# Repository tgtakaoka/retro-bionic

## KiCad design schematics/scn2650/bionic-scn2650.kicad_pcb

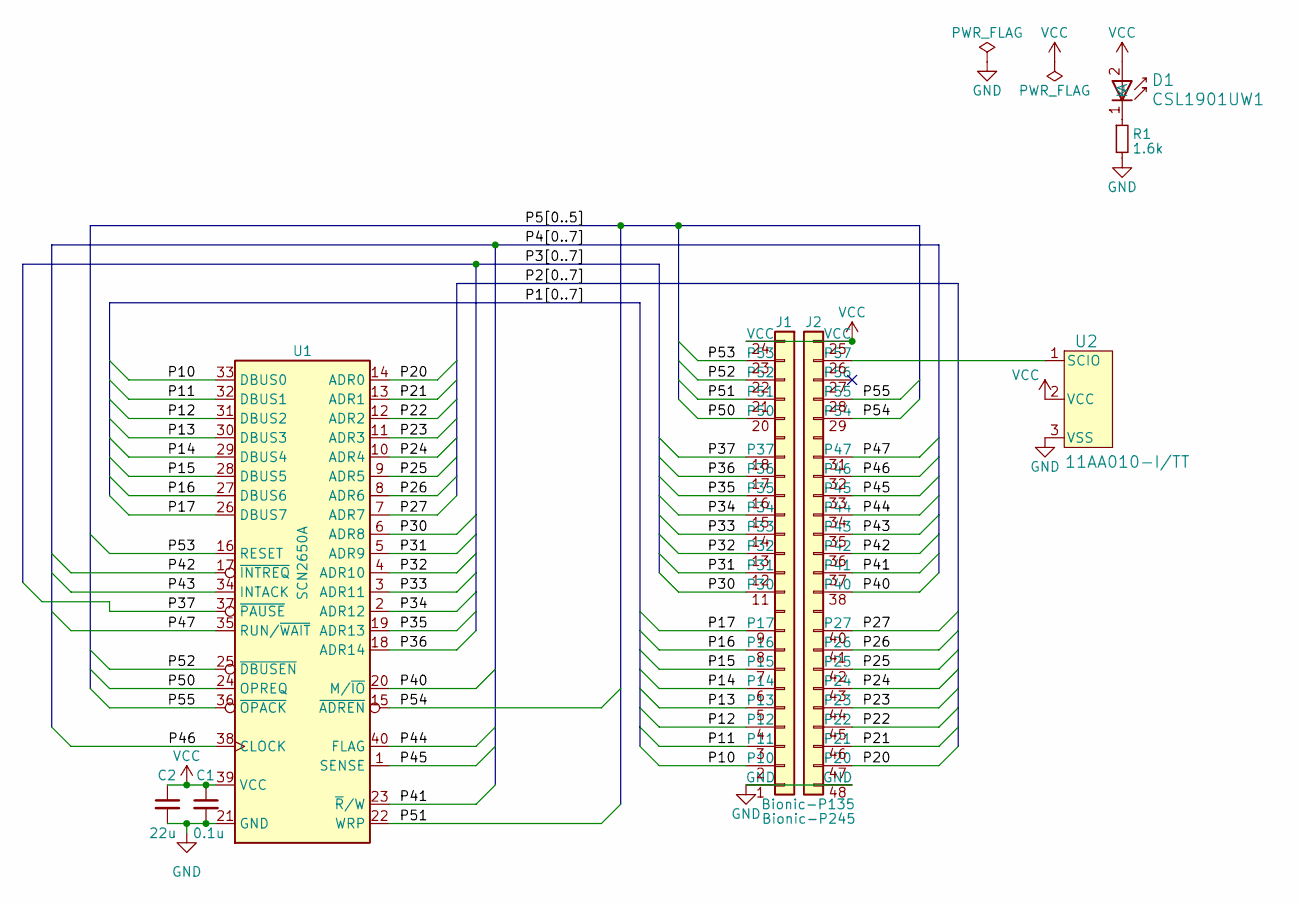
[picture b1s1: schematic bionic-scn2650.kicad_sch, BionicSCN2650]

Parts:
C1: 0.1u; C_0603_1608Metric_Pad1.08x0.95mm_HandSolder
C2: 22u; C_0603_1608Metric_Pad1.08x0.95mm_HandSolder
D1: CSL1901UW1; LED_CSL1901UW1_ROM-M
J1: Bionic-P135; Bionic-P135_THT
J2: Bionic-P245; Bionic-P245_THT
R1: 1.6k; R_0603_1608Metric_Pad0.98x0.95mm_HandSolder
U1: SCN2650A; DIP-40_W15.24mm_Socket
U2: 11AA010-I/TT; SOT-23_MC_MCH-M

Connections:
/P10: J1.2 (P10), U1.33 (DBUS0)
/P11: J1.3 (P11), U1.32 (DBUS1)
/P12: J1.4 (P12), U1.31 (DBUS2)
/P13: J1.5 (P13), U1.30 (DBUS3)
/P14: J1.6 (P14), U1.29 (DBUS4)
/P15: J1.7 (P15), U1.28 (DBUS5)
/P16: J1.8 (P16), U1.27 (DBUS6)
/P17: J1.9 (P17), U1.26 (DBUS7)
/P20: J2.47 (P20), U1.14 (ADR0)
/P21: J2.46 (P21), U1.13 (ADR1)
/P22: J2.45 (P22), U1.12 (ADR2)
/P23: J2.44 (P23), U1.11 (ADR3)
/P24: J2.43 (P24), U1.10 (ADR4)
/P25: J2.42 (P25), U1.9 (ADR5)
/P26: J2.41 (P26), U1.8 (ADR6)
/P27: J2.40 (P27), U1.7 (ADR7)
/P30: J1.11 (P30), U1.6 (ADR8)
/P31: J1.12 (P31), U1.5 (ADR9)
/P32: J1.13 (P32), U1.4 (ADR10)
/P33: J1.14 (P33), U1.3 (ADR11)
/P34: J1.15 (P34), U1.2 (ADR12)
/P35: J1.16 (P35), U1.19 (ADR13)
/P36: J1.17 (P36), U1.18 (ADR14)
/P37: J1.18 (P37), U1.37 (~PAUSE)
/P40: J2.38 (P40), U1.20 (M/~IO)
/P41: J2.37 (P41), U1.23 (~R/W)
/P42: J2.36 (P42), U1.17 (~INTREQ)
/P43: J2.35 (P43), U1.34 (INTACK)
/P44: J2.34 (P44), U1.40 (FLAG)
/P45: J2.33 (P45), U1.1 (SENSE)
/P46: J2.32 (P46), U1.38 (CLOCK)
/P47: J2.31 (P47), U1.35 (RUN/~WAIT)
/P50: J1.20 (P50), U1.24 (OPREQ)
/P51: J1.21 (P51), U1.22 (WRP)
/P52: J1.22 (P52), U1.25 (~DBUSEN)
/P53: J1.23 (P53), U1.16 (RESET)
/P54: J2.29 (P54), U1.15 (~ADREN)
/P55: J2.28 (P55), U1.36 (~OPACK)
GND: C1.2, C2.2, J1.1 (GND), J2.48 (GND), R1.2, U1.21 (GND), U2.3 (VSS)
unnamed: D1.1 (K), R1.1
unnamed: J2.26 (P57), U2.1 (SCIO)
VCC: C1.1, C2.1, D1.2 (A), J1.24 (VCC), J2.25 (VCC), U1.39 (VCC), U2.2 (VCC)

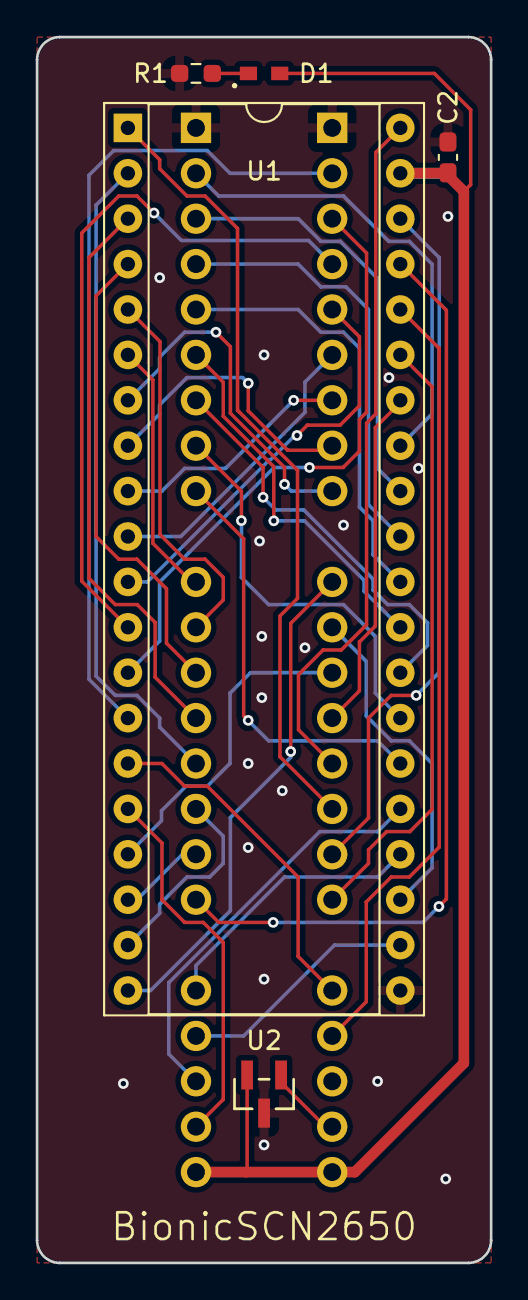
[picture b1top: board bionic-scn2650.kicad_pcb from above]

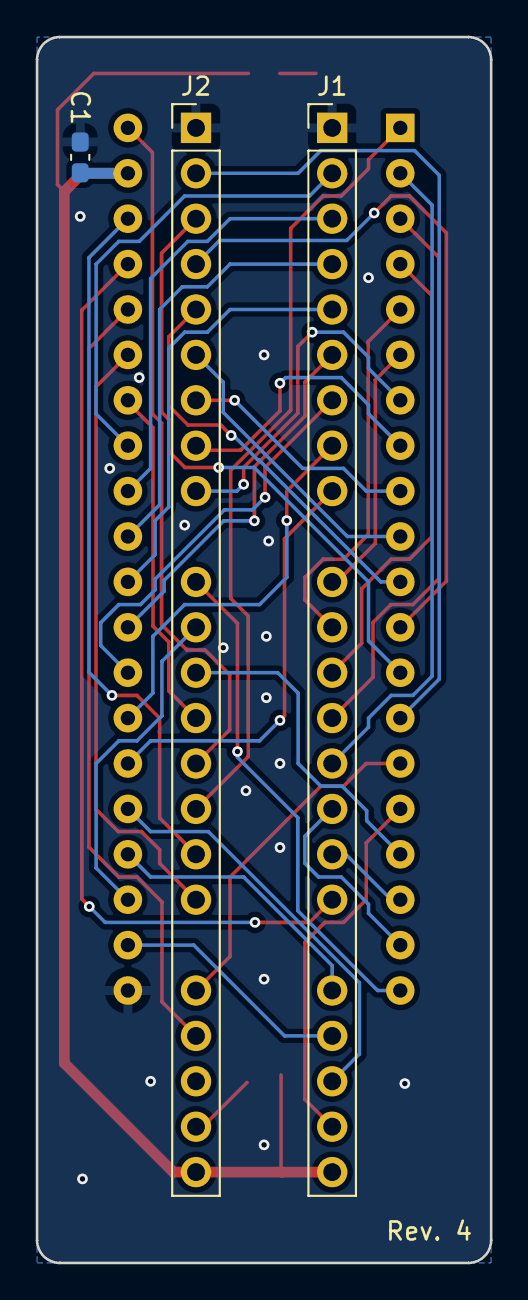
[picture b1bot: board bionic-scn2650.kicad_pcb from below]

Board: 2 copper layers, 25.4 x 68.6 mm, 8 parts (3 on the bottom side), 42 nets.

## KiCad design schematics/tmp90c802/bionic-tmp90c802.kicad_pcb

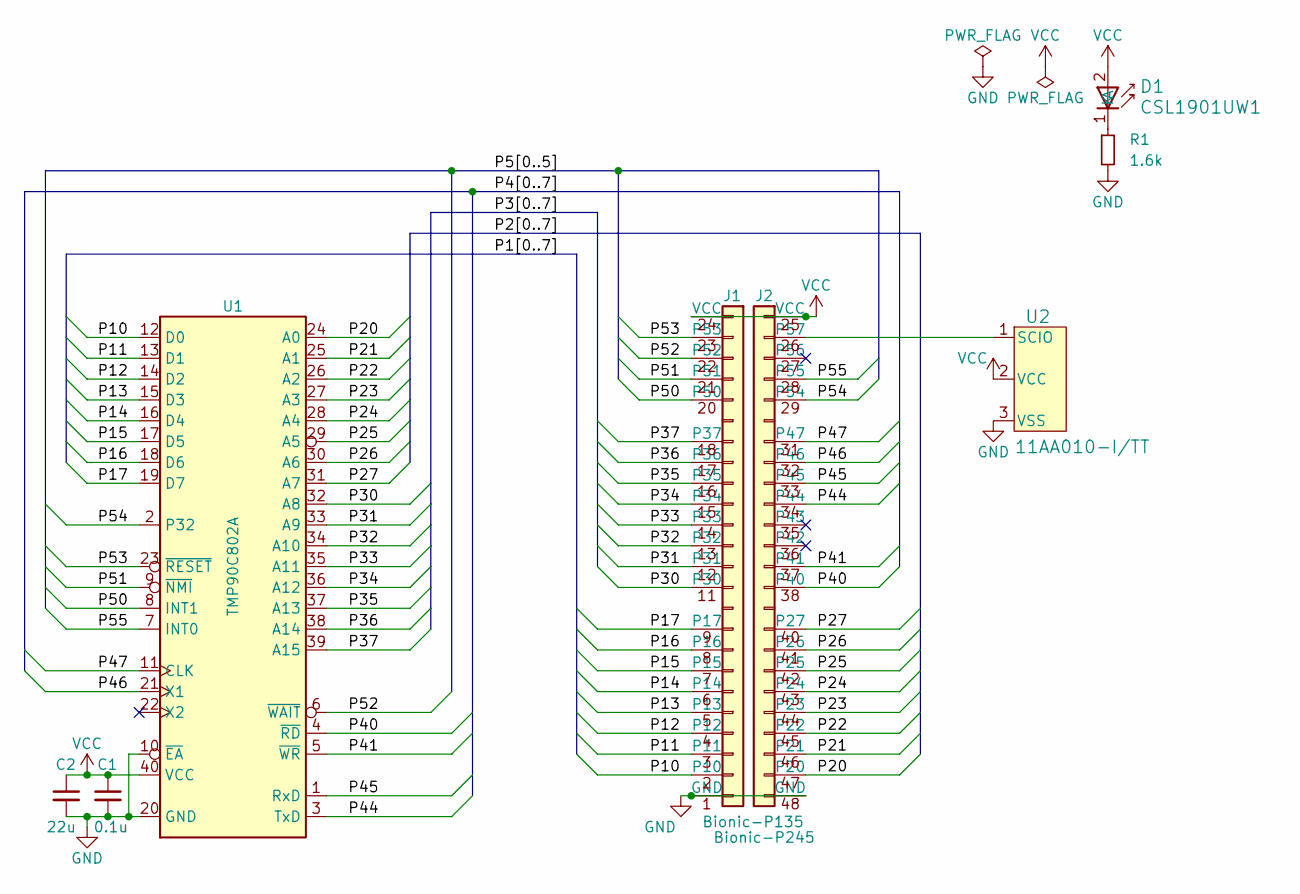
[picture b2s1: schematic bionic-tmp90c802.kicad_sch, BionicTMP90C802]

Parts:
C1: 0.1u; C_0603_1608Metric_Pad1.08x0.95mm_HandSolder
C2: 22u; C_0603_1608Metric_Pad1.08x0.95mm_HandSolder
D1: CSL1901UW1; LED_CSL1901UW1_ROM-M
J1: Bionic-P135; Bionic-P135_THT
J2: Bionic-P245; Bionic-P245_THT
R1: 1.6k; R_0603_1608Metric_Pad0.98x0.95mm_HandSolder
U1: TMP90C802A; DIP-40_W15.24mm_Socket
U2: 11AA010-I/TT; SOT-23_MC_MCH-M

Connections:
/P10: J1.2 (P10), U1.12 (D0)
/P11: J1.3 (P11), U1.13 (D1)
/P12: J1.4 (P12), U1.14 (D2)
/P13: J1.5 (P13), U1.15 (D3)
/P14: J1.6 (P14), U1.16 (D4)
/P15: J1.7 (P15), U1.17 (D5)
/P16: J1.8 (P16), U1.18 (D6)
/P17: J1.9 (P17), U1.19 (D7)
/P20: J2.47 (P20), U1.24 (A0)
/P21: J2.46 (P21), U1.25 (A1)
/P22: J2.45 (P22), U1.26 (A2)
/P23: J2.44 (P23), U1.27 (A3)
/P24: J2.43 (P24), U1.28 (A4)
/P25: J2.42 (P25), U1.29 (A5)
/P26: J2.41 (P26), U1.30 (A6)
/P27: J2.40 (P27), U1.31 (A7)
/P30: J1.11 (P30), U1.32 (A8)
/P31: J1.12 (P31), U1.33 (A9)
/P32: J1.13 (P32), U1.34 (A10)
/P33: J1.14 (P33), U1.35 (A11)
/P34: J1.15 (P34), U1.36 (A12)
/P35: J1.16 (P35), U1.37 (A13)
/P36: J1.17 (P36), U1.38 (A14)
/P37: J1.18 (P37), U1.39 (A15)
/P40: J2.38 (P40), U1.4 (~RD)
/P41: J2.37 (P41), U1.5 (~WR)
/P44: J2.34 (P44), U1.3 (TxD)
/P45: J2.33 (P45), U1.1 (RxD)
/P46: J2.32 (P46), U1.21 (X1)
/P47: J2.31 (P47), U1.11 (CLK)
/P50: J1.20 (P50), U1.8 (INT1)
/P51: J1.21 (P51), U1.9 (~NMI)
/P52: J1.22 (P52), U1.6 (~WAIT)
/P53: J1.23 (P53), U1.23 (~RESET)
/P54: J2.29 (P54), U1.2 (P32)
/P55: J2.28 (P55), U1.7 (INT0)
GND: C1.2, C2.2, J1.1 (GND), J2.48 (GND), R1.2, U1.10 (~EA), U1.20 (GND), U2.3 (VSS)
unnamed: D1.1 (K), R1.1
unnamed: J2.26 (P57), U2.1 (SCIO)
VCC: C1.1, C2.1, D1.2 (A), J1.24 (VCC), J2.25 (VCC), U1.40 (VCC), U2.2 (VCC)

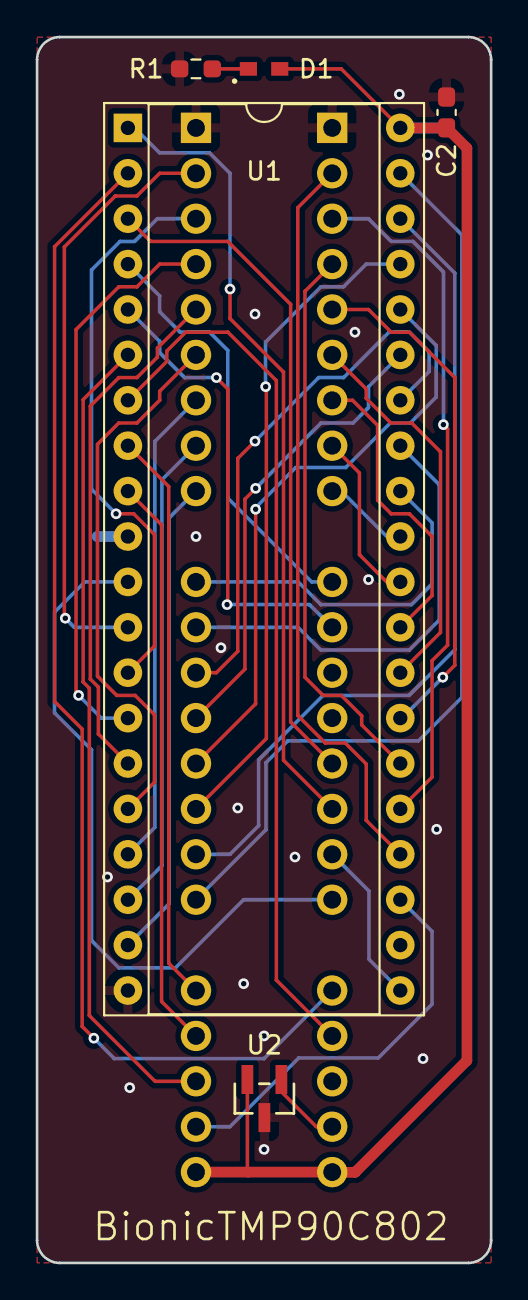
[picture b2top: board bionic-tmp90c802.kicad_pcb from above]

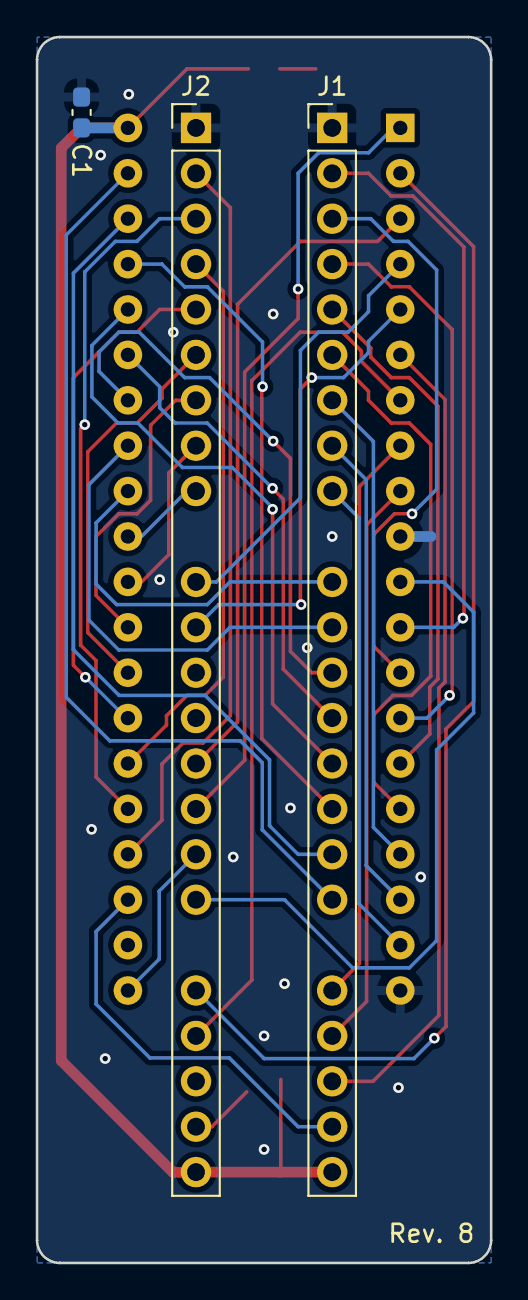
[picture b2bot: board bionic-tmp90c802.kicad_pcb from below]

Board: 2 copper layers, 25.4 x 68.6 mm, 8 parts (3 on the bottom side), 40 nets.

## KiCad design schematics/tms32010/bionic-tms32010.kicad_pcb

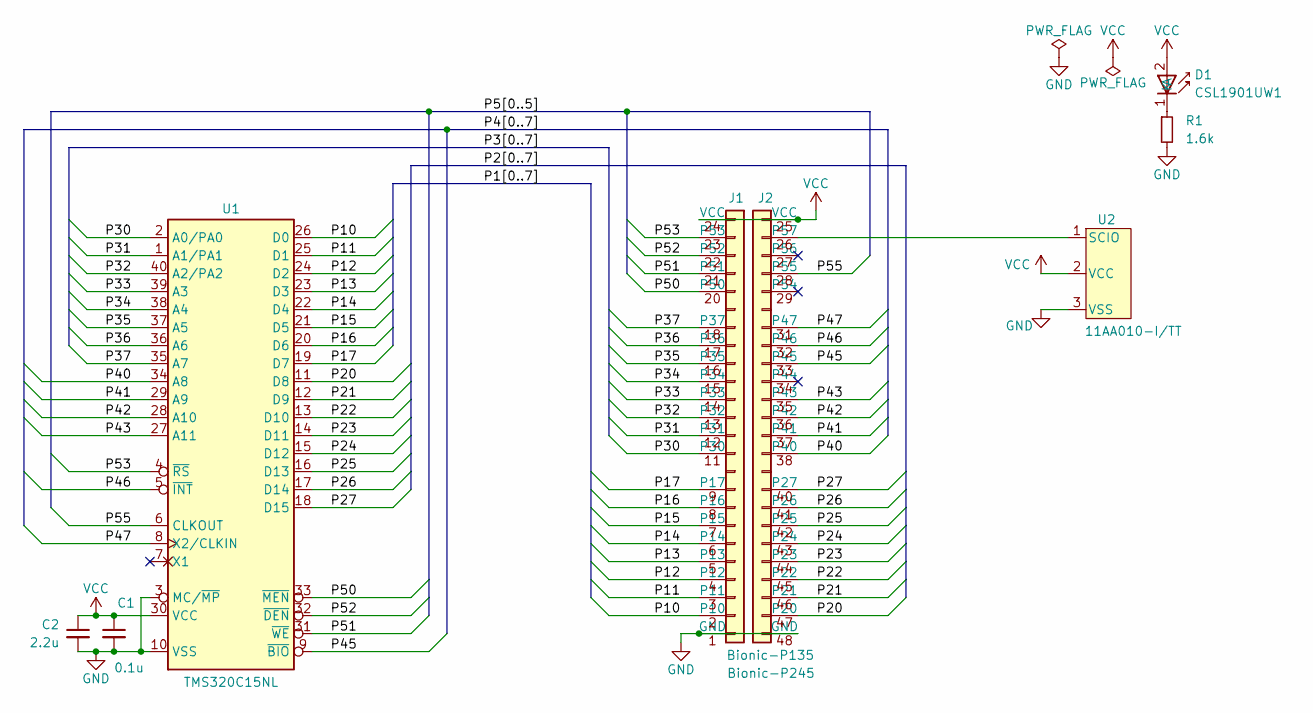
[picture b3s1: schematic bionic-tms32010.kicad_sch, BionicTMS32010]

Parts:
C1: 0.1u; C_0603_1608Metric_Pad1.08x0.95mm_HandSolder
C2: 2.2u; C_0603_1608Metric_Pad1.08x0.95mm_HandSolder
D1: CSL1901UW1; LED_CSL1901UW1_ROM-M
J1: Bionic-P135; Bionic-P135_THT
J2: Bionic-P245; Bionic-P245_THT
R1: 1.6k; R_0603_1608Metric_Pad0.98x0.95mm_HandSolder
U1: TMS320C15NL; DIP-40_W15.24mm_Socket
U2: 11AA010-I/TT; SOT-23_MC_MCH-M

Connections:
/P10: J1.2 (P10), U1.26 (D0)
/P11: J1.3 (P11), U1.25 (D1)
/P12: J1.4 (P12), U1.24 (D2)
/P13: J1.5 (P13), U1.23 (D3)
/P14: J1.6 (P14), U1.22 (D4)
/P15: J1.7 (P15), U1.21 (D5)
/P16: J1.8 (P16), U1.20 (D6)
/P17: J1.9 (P17), U1.19 (D7)
/P20: J2.47 (P20), U1.11 (D8)
/P21: J2.46 (P21), U1.12 (D9)
/P22: J2.45 (P22), U1.13 (D10)
/P23: J2.44 (P23), U1.14 (D11)
/P24: J2.43 (P24), U1.15 (D12)
/P25: J2.42 (P25), U1.16 (D13)
/P26: J2.41 (P26), U1.17 (D14)
/P27: J2.40 (P27), U1.18 (D15)
/P30: J1.11 (P30), U1.2 (A0/PA0)
/P31: J1.12 (P31), U1.1 (A1/PA1)
/P32: J1.13 (P32), U1.40 (A2/PA2)
/P33: J1.14 (P33), U1.39 (A3)
/P34: J1.15 (P34), U1.38 (A4)
/P35: J1.16 (P35), U1.37 (A5)
/P36: J1.17 (P36), U1.36 (A6)
/P37: J1.18 (P37), U1.35 (A7)
/P40: J2.38 (P40), U1.34 (A8)
/P41: J2.37 (P41), U1.29 (A9)
/P42: J2.36 (P42), U1.28 (A10)
/P43: J2.35 (P43), U1.27 (A11)
/P45: J2.33 (P45), U1.9 (~BIO)
/P46: J2.32 (P46), U1.5 (~INT)
/P47: J2.31 (P47), U1.8 (X2/CLKIN)
/P50: J1.20 (P50), U1.33 (~MEN)
/P51: J1.21 (P51), U1.31 (~WE)
/P52: J1.22 (P52), U1.32 (~DEN)
/P53: J1.23 (P53), U1.4 (~RS)
/P55: J2.28 (P55), U1.6 (CLKOUT)
GND: C1.2, C2.2, J1.1 (GND), J2.48 (GND), R1.2, U1.3 (MC/~MP), U1.10 (VSS), U2.3 (VSS)
unnamed: D1.1 (K), R1.1
unnamed: J2.26 (P57), U2.1 (SCIO)
VCC: C1.1, C2.1, D1.2 (A), J1.24 (VCC), J2.25 (VCC), U1.30 (VCC), U2.2 (VCC)

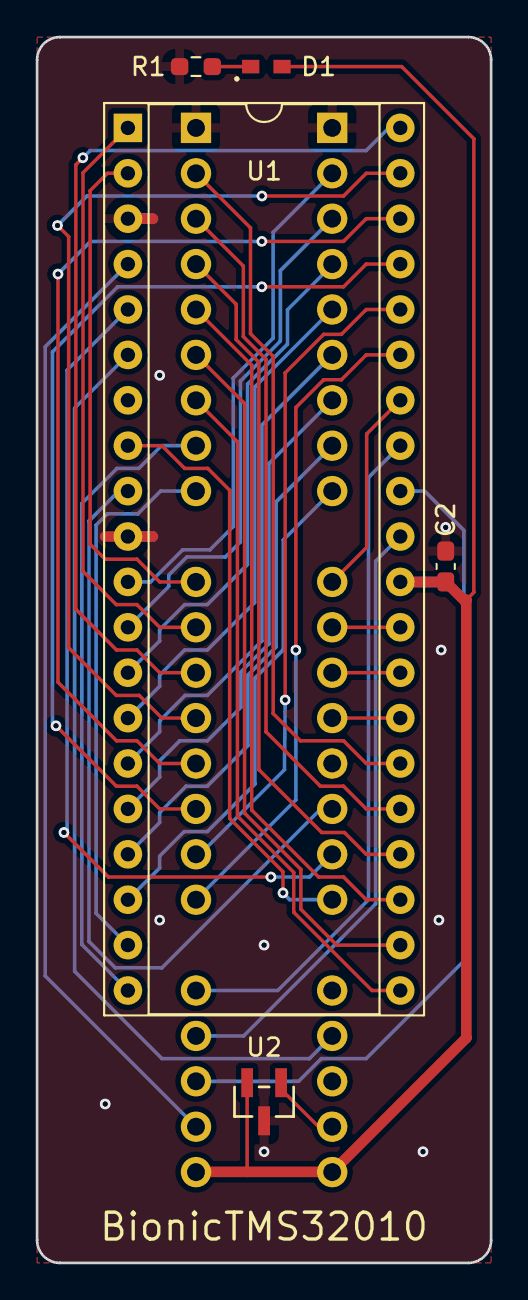
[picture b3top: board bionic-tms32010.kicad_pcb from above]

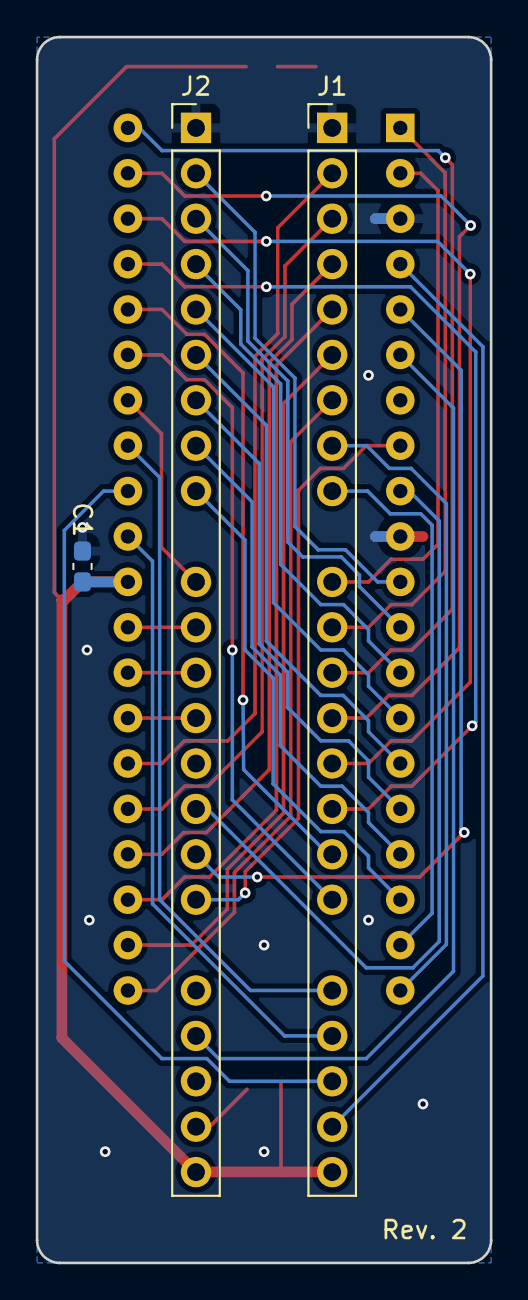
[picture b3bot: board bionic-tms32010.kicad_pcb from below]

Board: 2 copper layers, 25.4 x 68.6 mm, 8 parts (3 on the bottom side), 40 nets.

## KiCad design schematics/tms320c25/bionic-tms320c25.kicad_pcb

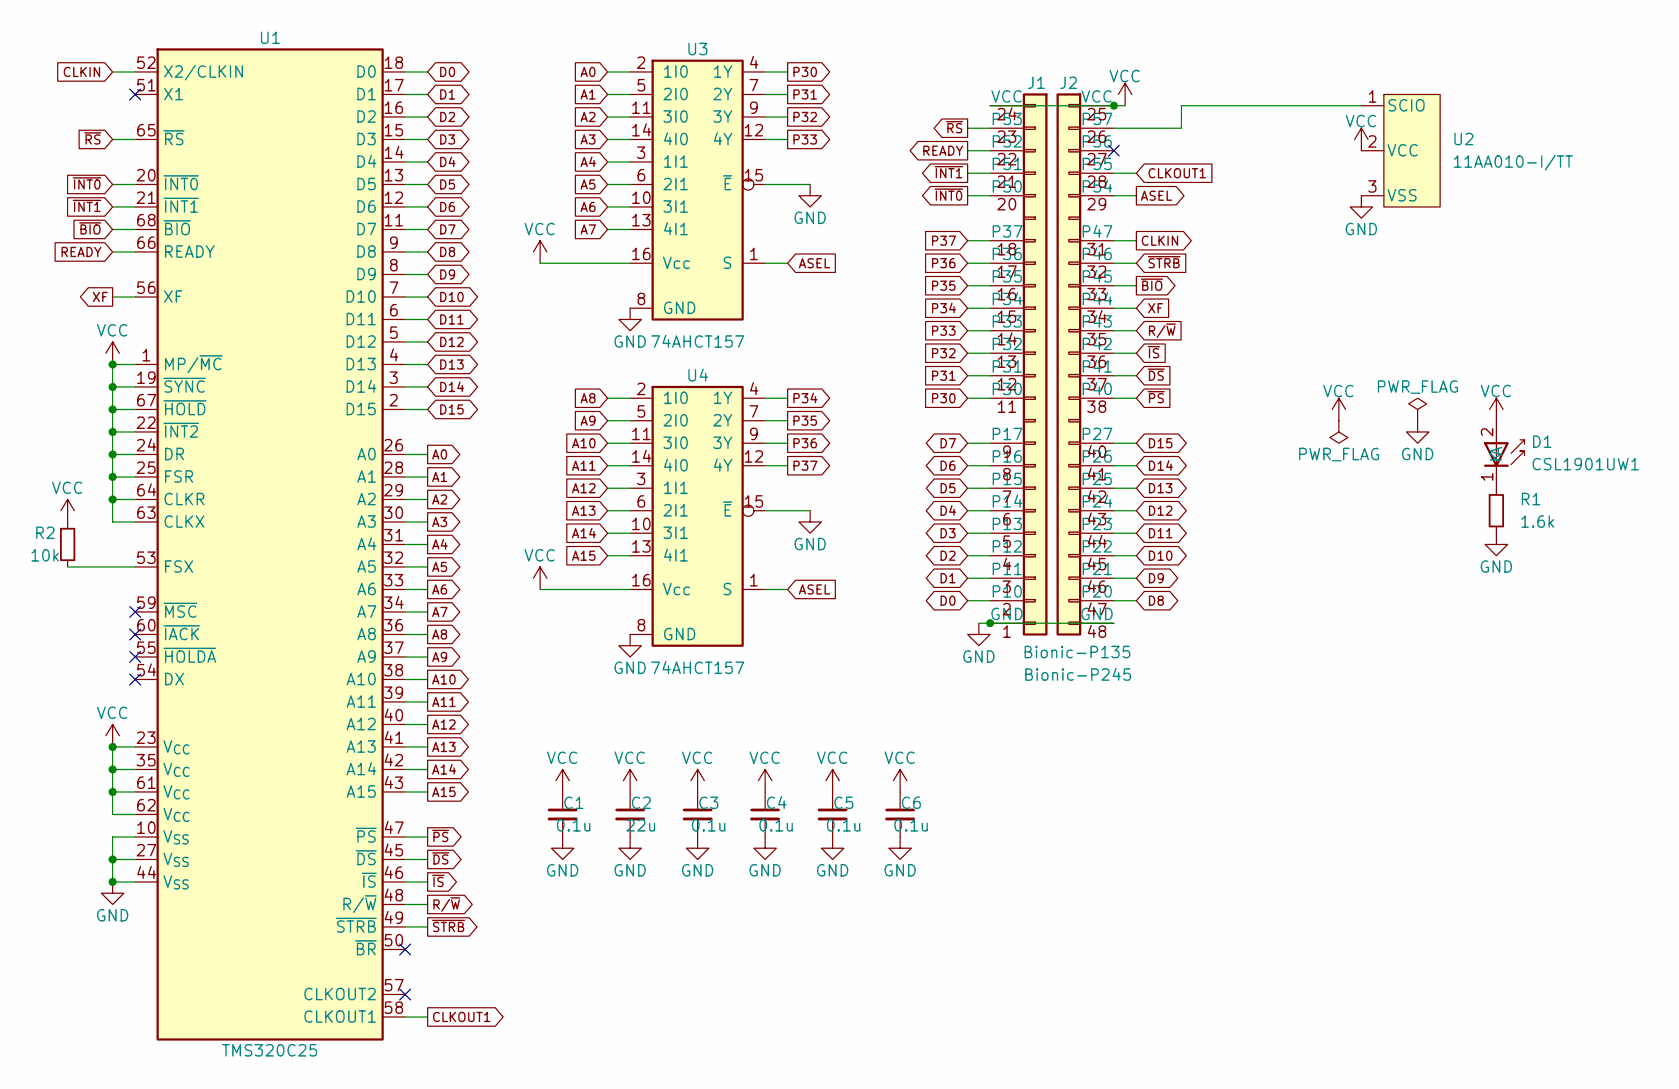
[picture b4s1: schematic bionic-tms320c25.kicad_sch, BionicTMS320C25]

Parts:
C1, C3, C4, C5, C6: 0.1u; C_0603_1608Metric_Pad1.08x0.95mm_HandSolder
C2: 22u; C_0603_1608Metric_Pad1.08x0.95mm_HandSolder
D1: CSL1901UW1; LED_CSL1901UW1_ROM-M
J1: Bionic-P135; Bionic-P135_SMT
J2: Bionic-P245; Bionic-P245_SMT
R1: 1.6k; R_0603_1608Metric_Pad0.98x0.95mm_HandSolder
R2: 10k; R_0603_1608Metric_Pad0.98x0.95mm_HandSolder
U1: TMS320C25; 846821B1RKTP
U2: 11AA010-I/TT; SOT-23_MC_MCH-M
U3, U4: 74AHCT157; PW16-M

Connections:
A0: U1.26 (HSI.2/HSO.4), U3.2 (1I0)
A1: U1.28 (HSO.0), U3.5 (2I0)
A2: U1.29 (HSO.1), U3.11 (3I0)
A3: U1.30 (P1.5), U3.14 (4I0)
A4: U1.31 (P1.6), U3.3 (1I1)
A5: U1.32 (P1.7), U3.6 (2I1)
A6: U1.33 (P2.6), U3.10 (3I1)
A7: U1.34 (HSO.2), U3.13 (4I1)
A8: U1.36 (V_{SS}), U4.2 (1I0)
A9: U1.37 (V_{PP}), U4.5 (2I0)
A10: U1.38 (P2.7), U4.11 (3I0)
A11: U1.39 (P2.5/PWM), U4.14 (4I0)
A12: U1.40 (~WRL/~WR), U4.3 (1I1)
A13: U1.41 (~WRH/~BHE), U4.6 (2I1)
A14: U1.42 (P2.4/T2RST), U4.10 (3I1)
A15: U1.43 (READY), U4.13 (4I1)
ASEL: J2.29 (P54), U3.1 (S), U4.1 (S)
CLKIN: J2.31 (P47), U1.52 (AD8)
CLKOUT1: J2.28 (P55), U1.58 (AD2)
D0: J1.2 (P10), U1.18 (P2.0/TxD)
D1: J1.3 (P11), U1.17 (P2.1/RxD)
D2: J1.4 (P12), U1.16 (~RESET)
D3: J1.5 (P13), U1.15 (P2.2/EXINT)
D4: J1.6 (P14), U1.14 (V_{PD})
D5: J1.7 (P15), U1.13 (V_{REF})
D6: J1.8 (P16), U1.12 (ANGND)
D7: J1.9 (P17), U1.11 (ACH4)
D8: J2.47 (P20), U1.9 (ACH7)
D9: J2.46 (P21), U1.8 (ACH6)
D10: J2.45 (P22), U1.7 (ACH2)
D11: J2.44 (P23), U1.6 (ACH0)
D12: J2.43 (P24), U1.5 (ACH1)
D13: J2.42 (P25), U1.4 (ACH3)
D14: J2.41 (P26), U1.3 (NMI)
D15: J2.40 (P27), U1.2 (~EA)
GND: C1.2, C2.2, C3.2, C4.2, C5.2, C6.2, J1.1 (GND), J2.48 (GND), R1.2, U1.10 (ACH5), U1.27 (HSI.3/HSO.5), U1.44 (P2.3/T2CLK), U2.3 (VSS), U3.8 (GND), U3.15 (~E), U4.8 (GND), U4.15 (~E)
unnamed: D1.1 (K), R1.1
unnamed: J2.26 (P57), U2.1 (SCIO)
unnamed: R2.2, U1.53 (AD7)
P30: J1.11 (P30), U3.4 (1Y)
P31: J1.12 (P31), U3.7 (2Y)
P32: J1.13 (P32), U3.9 (3Y)
P33: J1.14 (P33), U3.12 (4Y)
P34: J1.15 (P34), U4.4 (1Y)
P35: J1.16 (P35), U4.7 (2Y)
P36: J1.17 (P36), U4.9 (3Y)
P37: J1.18 (P37), U4.12 (4Y)
READY: J1.22 (P52), U1.66 (XTAL2)
R/~W: J2.35 (P43), U1.48 (AD12)
VCC: C1.1, C2.1, C3.1, C4.1, C5.1, C6.1, D1.2 (A), J1.24 (VCC), J2.25 (VCC), R2.1, U1.1 (V_{CC}), U1.19 (P1.0), U1.22 (P1.3), U1.23 (P1.4), U1.24 (HSI.0), U1.25 (HSI.1), U1.35 (HSO.3), U1.61 (~RD), U1.62 (~ALE/~ADV), U1.63 (INST), U1.64 (BUSWIDTH), U1.67 (XTAL1), U2.2 (VCC), U3.16 (Vcc), U4.16 (Vcc)
XF: J2.34 (P44), U1.56 (AD4)
~BIO: J2.33 (P45), U1.68 (V_{SS})
~DS: J2.37 (P41), U1.45 (AD15)
~INT0: J1.20 (P50), U1.20 (P1.1)
~INT1: J1.21 (P51), U1.21 (P1.2)
~IS: J2.36 (P42), U1.46 (AD14)
~PS: J2.38 (P40), U1.47 (AD13)
~RS: J1.23 (P53), U1.65 (CLKOUT)
~STRB: J2.32 (P46), U1.49 (AD11)

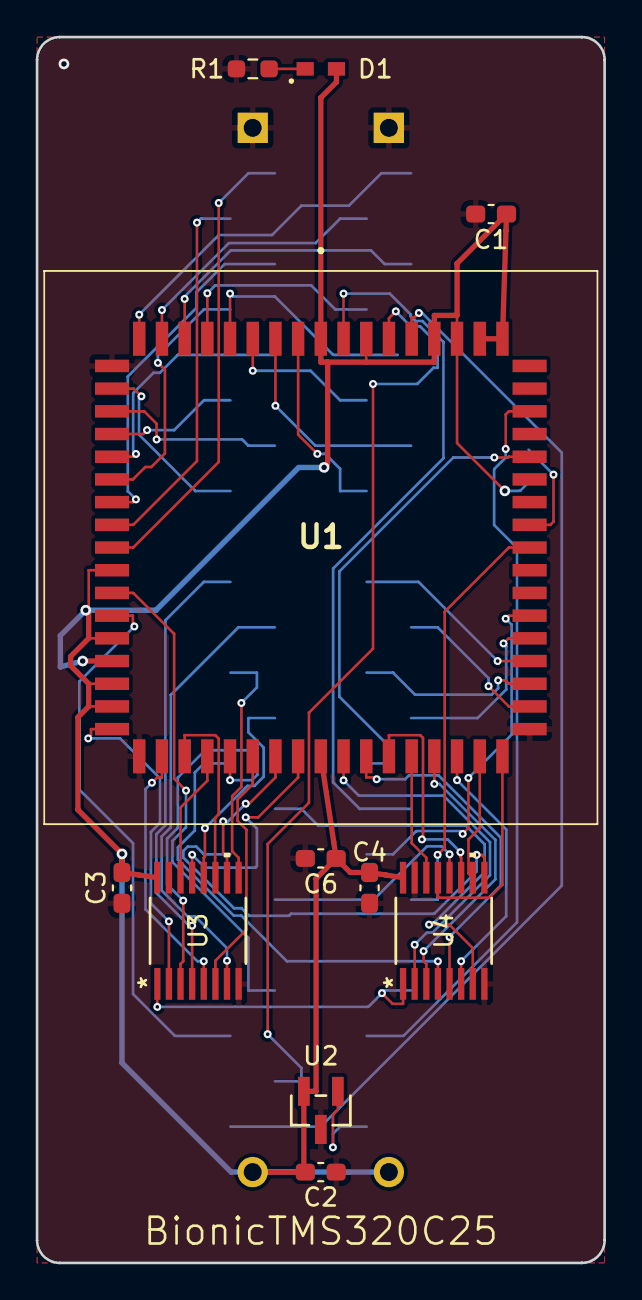
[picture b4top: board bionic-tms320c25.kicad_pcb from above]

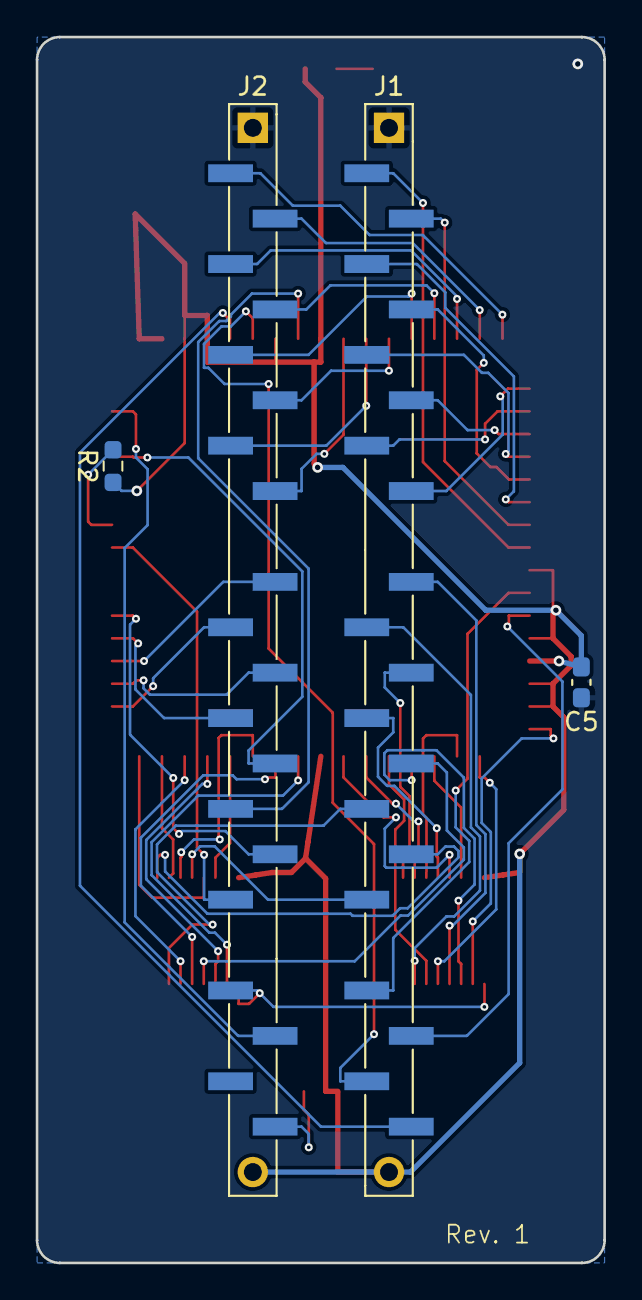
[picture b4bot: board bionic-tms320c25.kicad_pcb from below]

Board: 2 copper layers, 31.8 x 68.6 mm, 15 parts (4 on the bottom side), 59 nets.

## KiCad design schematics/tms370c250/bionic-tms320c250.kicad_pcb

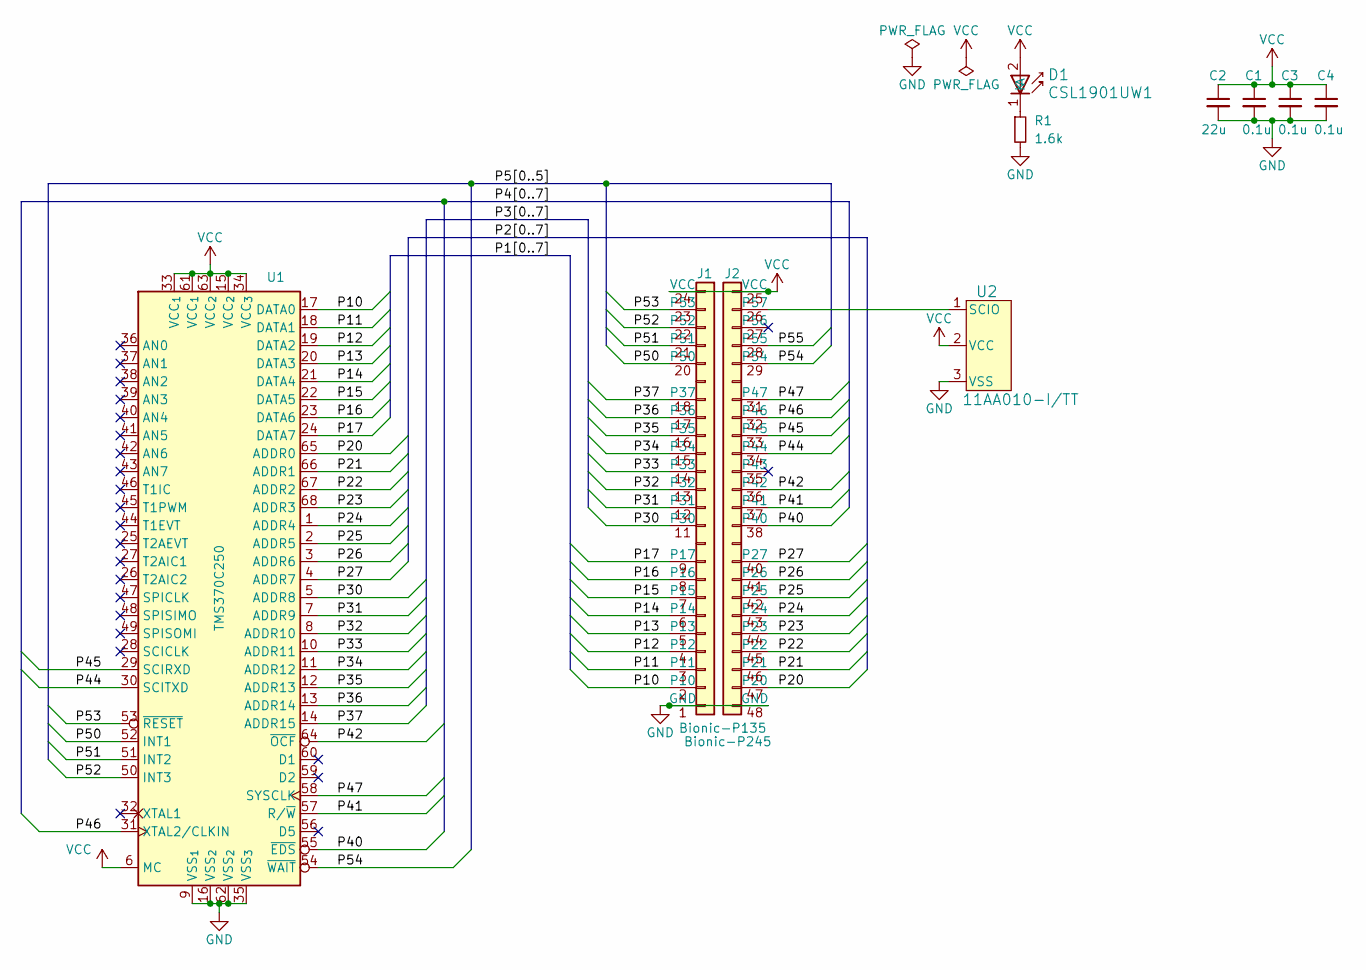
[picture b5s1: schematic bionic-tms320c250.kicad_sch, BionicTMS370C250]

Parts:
C1, C3, C4: 0.1u; C_0603_1608Metric_Pad1.08x0.95mm_HandSolder
C2: 22u; C_0603_1608Metric_Pad1.08x0.95mm_HandSolder
D1: CSL1901UW1; LED_CSL1901UW1_ROM-M
J1: Bionic-P135; Bionic-P135_SMT
J2: Bionic-P245; Bionic-P245_SMT
R1: 1.6k; R_0603_1608Metric_Pad0.98x0.95mm_HandSolder
U1: TMS370C250; 846821B1RKTP
U2: 11AA010-I/TT; SOT-23_MC_MCH-M

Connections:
/P10: J1.2 (P10), U1.17 (DATA0)
/P11: J1.3 (P11), U1.18 (DATA1)
/P12: J1.4 (P12), U1.19 (DATA2)
/P13: J1.5 (P13), U1.20 (DATA3)
/P14: J1.6 (P14), U1.21 (DATA4)
/P15: J1.7 (P15), U1.22 (DATA5)
/P16: J1.8 (P16), U1.23 (DATA6)
/P17: J1.9 (P17), U1.24 (DATA7)
/P20: J2.47 (P20), U1.65 (ADDR0)
/P21: J2.46 (P21), U1.66 (ADDR1)
/P22: J2.45 (P22), U1.67 (ADDR2)
/P23: J2.44 (P23), U1.68 (ADDR3)
/P24: J2.43 (P24), U1.1 (ADDR4)
/P25: J2.42 (P25), U1.2 (ADDR5)
/P26: J2.41 (P26), U1.3 (ADDR6)
/P27: J2.40 (P27), U1.4 (ADDR7)
/P30: J1.11 (P30), U1.5 (ADDR8)
/P31: J1.12 (P31), U1.7 (ADDR9)
/P32: J1.13 (P32), U1.8 (ADDR10)
/P33: J1.14 (P33), U1.10 (ADDR11)
/P34: J1.15 (P34), U1.11 (ADDR12)
/P35: J1.16 (P35), U1.12 (ADDR13)
/P36: J1.17 (P36), U1.13 (ADDR14)
/P37: J1.18 (P37), U1.14 (ADDR15)
/P40: J2.38 (P40), U1.55 (~EDS)
/P41: J2.37 (P41), U1.57 (R/~W)
/P42: J2.36 (P42), U1.64 (~OCF)
/P44: J2.34 (P44), U1.30 (SCITXD)
/P45: J2.33 (P45), U1.29 (SCIRXD)
/P46: J2.32 (P46), U1.31 (XTAL2/CLKIN)
/P47: J2.31 (P47), U1.58 (SYSCLK)
/P50: J1.20 (P50), U1.52 (INT1)
/P51: J1.21 (P51), U1.51 (INT2)
/P52: J1.22 (P52), U1.50 (INT3)
/P53: J1.23 (P53), U1.53 (~RESET)
/P54: J2.29 (P54), U1.54 (~WAIT)
/P55: J2.28 (P55)
GND: C1.2, C2.2, C3.2, C4.2, J1.1 (GND), J2.48 (GND), R1.2, U1.9 (VSS_{1}), U1.16 (VSS_{2}), U1.35 (VSS_{3}), U1.62 (VSS_{2}), U2.3 (VSS)
unnamed: D1.1 (K), R1.1
unnamed: J2.26 (P57), U2.1 (SCIO)
VCC: C1.1, C2.1, C3.1, C4.1, D1.2 (A), J1.24 (VCC), J2.25 (VCC), U1.6 (MC), U1.15 (VCC_{2}), U1.33 (VCC_{1}), U1.34 (VCC_{3}), U1.61 (VCC_{1}), U1.63 (VCC_{2}), U2.2 (VCC)

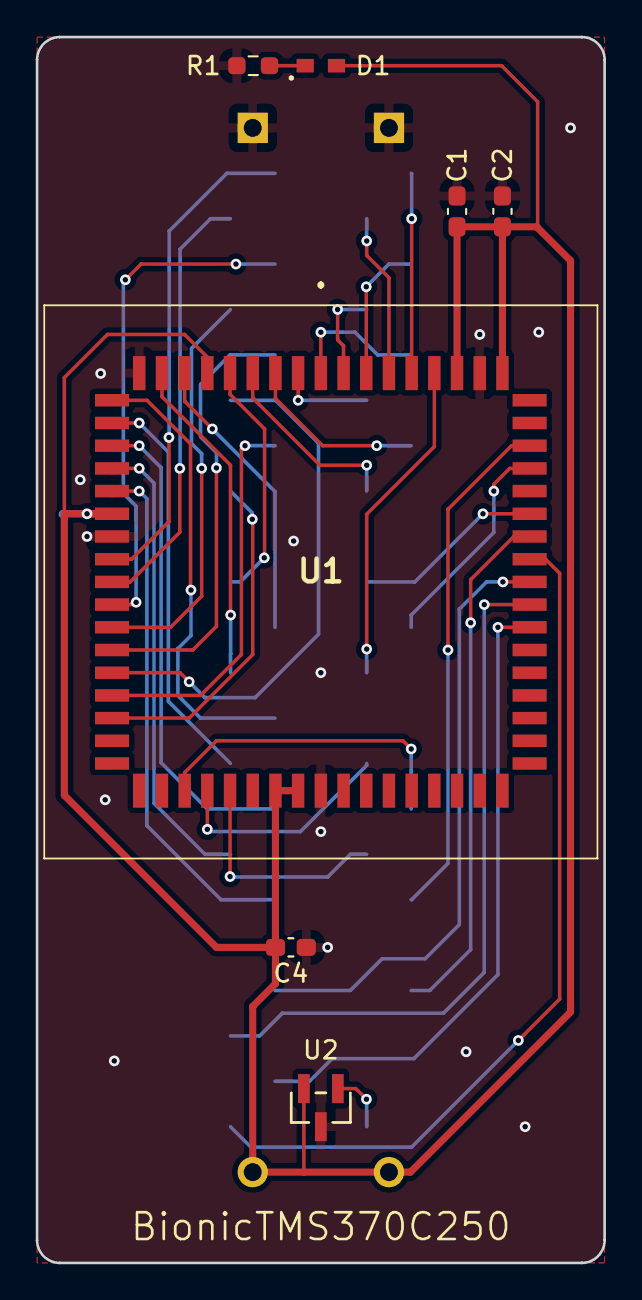
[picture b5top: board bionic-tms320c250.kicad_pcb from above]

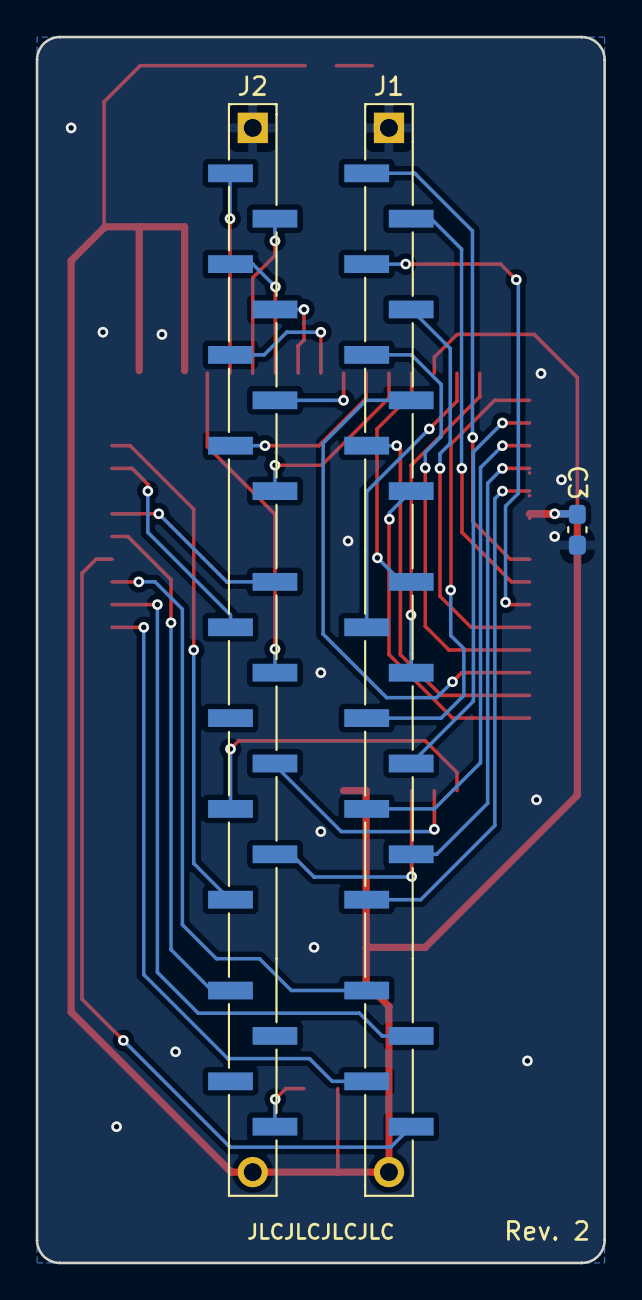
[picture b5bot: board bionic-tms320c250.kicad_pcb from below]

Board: 2 copper layers, 31.7 x 68.6 mm, 10 parts (3 on the bottom side), 40 nets.

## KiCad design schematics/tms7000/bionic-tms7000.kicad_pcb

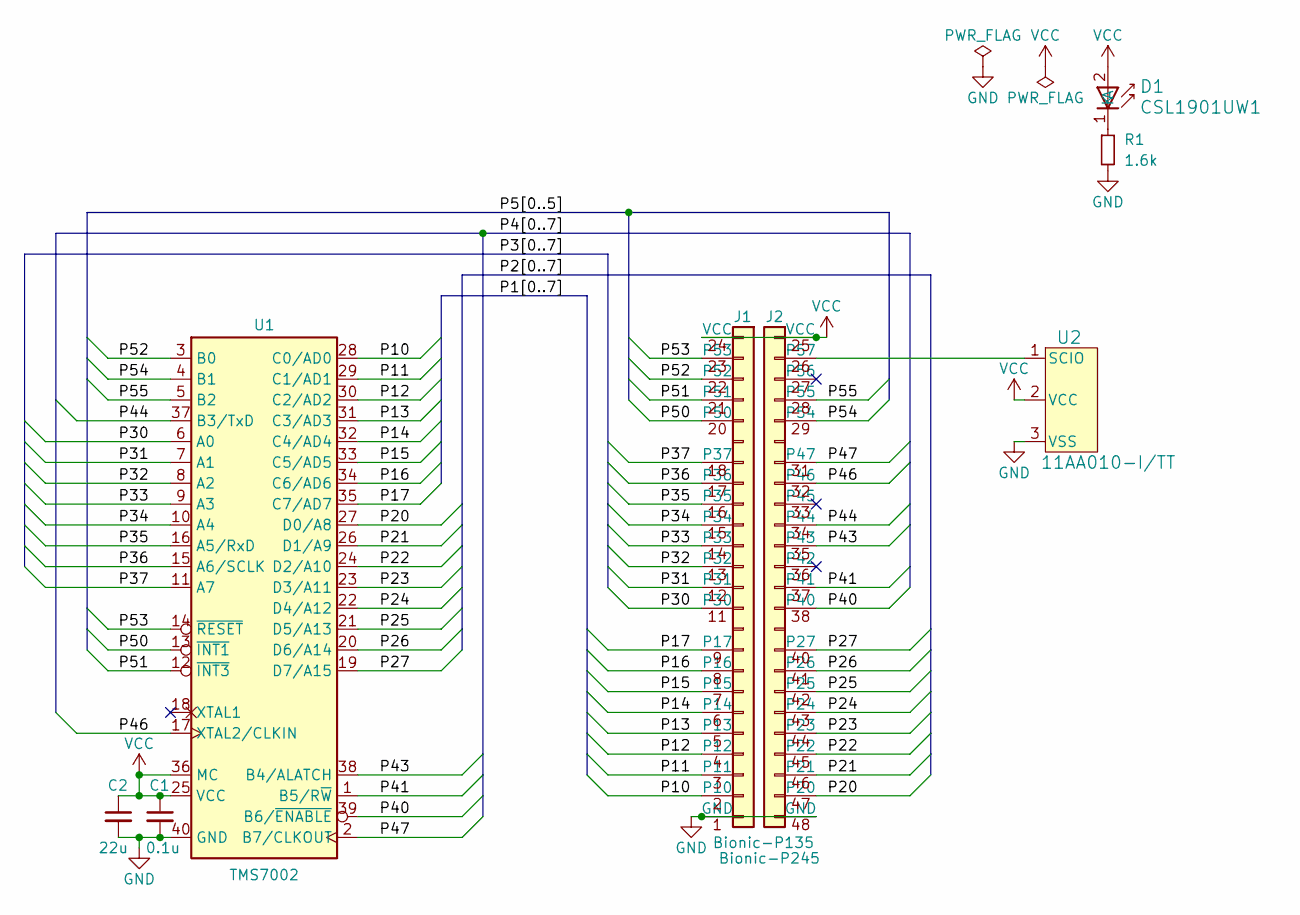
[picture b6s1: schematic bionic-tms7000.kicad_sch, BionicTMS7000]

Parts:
C1: 0.1u; C_0603_1608Metric_Pad1.08x0.95mm_HandSolder
C2: 22u; C_0603_1608Metric_Pad1.08x0.95mm_HandSolder
D1: CSL1901UW1; LED_CSL1901UW1_ROM-M
J1: Bionic-P135; Bionic-P135_THT
J2: Bionic-P245; Bionic-P245_THT
R1: 1.6k; R_0603_1608Metric_Pad0.98x0.95mm_HandSolder
U1: TMS7002; DIP-40_W15.24mm_Socket
U2: 11AA010-I/TT; SOT-23_MC_MCH-M

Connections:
/P10: J1.2 (P10), U1.28 (C0/AD0)
/P11: J1.3 (P11), U1.29 (C1/AD1)
/P12: J1.4 (P12), U1.30 (C2/AD2)
/P13: J1.5 (P13), U1.31 (C3/AD3)
/P14: J1.6 (P14), U1.32 (C4/AD4)
/P15: J1.7 (P15), U1.33 (C5/AD5)
/P16: J1.8 (P16), U1.34 (C6/AD6)
/P17: J1.9 (P17), U1.35 (C7/AD7)
/P20: J2.47 (P20), U1.27 (D0/A8)
/P21: J2.46 (P21), U1.26 (D1/A9)
/P22: J2.45 (P22), U1.24 (D2/A10)
/P23: J2.44 (P23), U1.23 (D3/A11)
/P24: J2.43 (P24), U1.22 (D4/A12)
/P25: J2.42 (P25), U1.21 (D5/A13)
/P26: J2.41 (P26), U1.20 (D6/A14)
/P27: J2.40 (P27), U1.19 (D7/A15)
/P30: J1.11 (P30), U1.6 (A0)
/P31: J1.12 (P31), U1.7 (A1)
/P32: J1.13 (P32), U1.8 (A2)
/P33: J1.14 (P33), U1.9 (A3)
/P34: J1.15 (P34), U1.10 (A4)
/P35: J1.16 (P35), U1.16 (A5/RxD)
/P36: J1.17 (P36), U1.15 (A6/SCLK)
/P37: J1.18 (P37), U1.11 (A7)
/P40: J2.38 (P40), U1.39 (B6/~ENABLE)
/P41: J2.37 (P41), U1.1 (B5/R~W)
/P43: J2.35 (P43), U1.38 (B4/ALATCH)
/P44: J2.34 (P44), U1.37 (B3/TxD)
/P46: J2.32 (P46), U1.17 (XTAL2/CLKIN)
/P47: J2.31 (P47), U1.2 (B7/CLKOUT)
/P50: J1.20 (P50), U1.13 (~INT1)
/P51: J1.21 (P51), U1.12 (~INT3)
/P52: J1.22 (P52), U1.3 (B0)
/P53: J1.23 (P53), U1.14 (~RESET)
/P54: J2.29 (P54), U1.4 (B1)
/P55: J2.28 (P55), U1.5 (B2)
GND: C1.2, C2.2, J1.1 (GND), J2.48 (GND), R1.2, U1.40 (GND), U2.3 (VSS)
unnamed: D1.1 (K), R1.1
unnamed: J2.26 (P57), U2.1 (SCIO)
VCC: C1.1, C2.1, D1.2 (A), J1.24 (VCC), J2.25 (VCC), U1.25 (VCC), U1.36 (MC), U2.2 (VCC)
